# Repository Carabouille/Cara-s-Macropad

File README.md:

# Cara-s-Macropad
my awesome DIY macropad for the hackpad project. Using a screen OLED, 6 switchs, a EC11 and some LEDs

## CAD

I know what you're thinking. and I agree with you it's not very handsome.
BUT I discover this project less than a week ago and with a deadline of January 1 and Christmas, New years.... I don't have time to really make a nice case ;-;

The inserts for the screws do not appear here, but they will of course be added before printing.

However, I am motivated to improve this CAD after the holidays.

I used Solidworks because Fusion is... is Fusion :)

in french we often say "en sah Fusion ca pue sa mère quand meme"

to explain a little bit about what I have in my mind : 

I draw this, and the final version should look like this with the UwU logo on the right

## PCB 
I used KiCad and I tried to make a compact pcb(under 10 x 10cm) with private jokes with my friends and a logo with my nickname "Cara"

IMPORTANT POINT !!!!!
you can see on the electrical sketch that I used some Leds but they do not appear on the PCB that's normal
I added an output for the LEDs below the encoder. I want to use the Leds around the pcb to make an effect that diffuse the light with a fit layer of PLA
So the LEDs should not appear on the PCB.

## Firmware

I'm not good at Pyhton so I asked my friends Pylou to help me with the code
It's pretty simple right now but I would improve everything once I have the card in my hand.
maybe change the language from python to C.

## BOM

Here's the list of parts for my project!

 - 1x Seeed XIAO RP2040
 - 6x Through-hole 1N4148 Diodes
 - 6x MX-Style switches
 - 1x EC11 Rotary encoders
 - 1x 0.91 inch OLED displays
 - 6x Blank DSA keycaps (White)
 - 14x SK6812 MINI-E LEDs
 - 4x M3x16mm screws
 - 4x M3x5mx4mm heatset inserts
 - 1x 3D printed case: not shure about the color
 - 1x PCB

## Special thanks

I want to thank my friend Pylou (love u my boy) for introducing me to the project (a little bit late :)))

thanks to the HackLab community the goatest community 

thanks to my mum for creating me

thanks Guyom, for not doing anything special on this project

thanks David Mercier, to help me to become a great hacker 

Thanks to photosynthesis for creating the oxygen that I breathe

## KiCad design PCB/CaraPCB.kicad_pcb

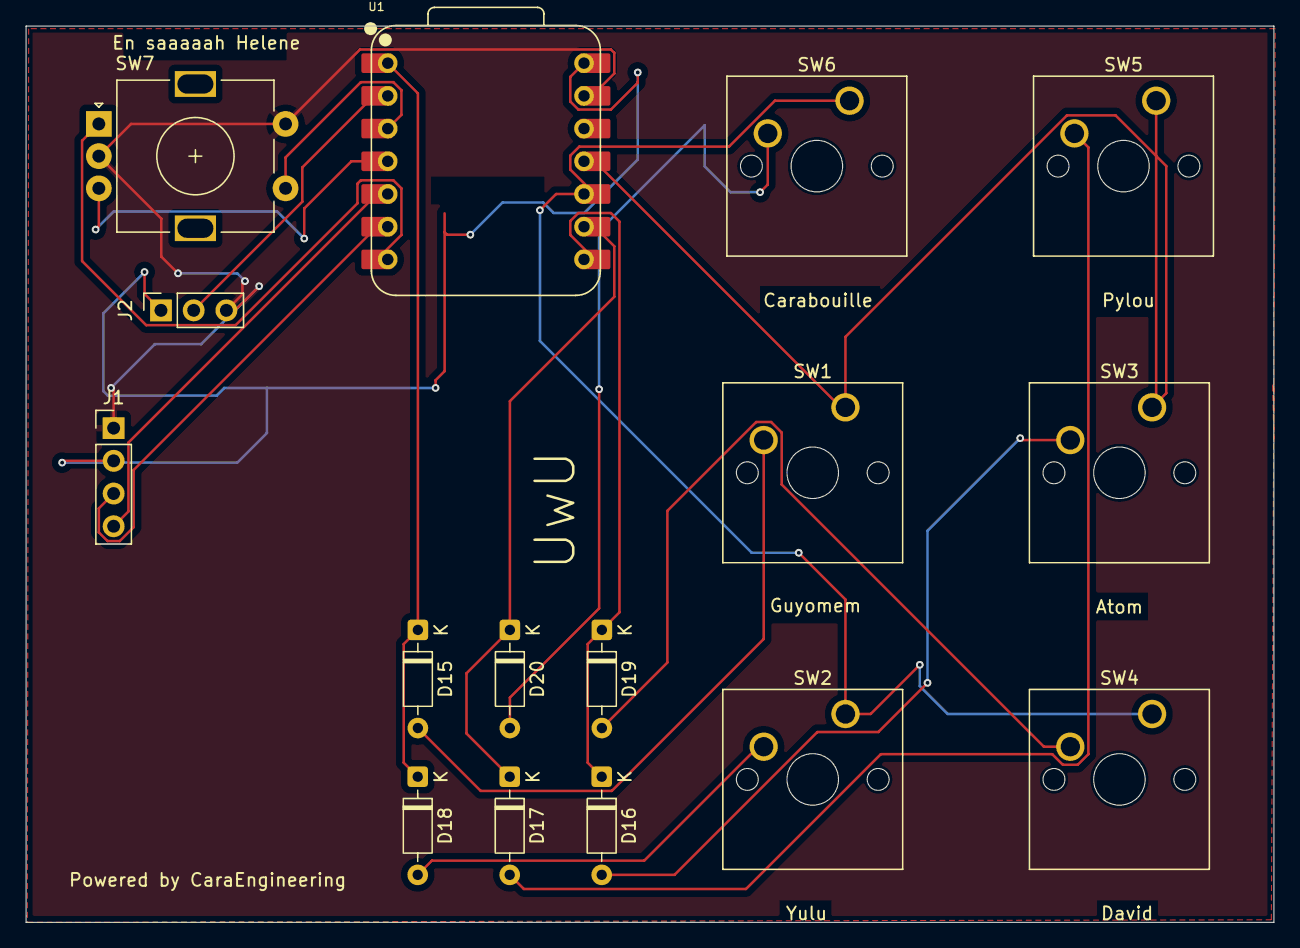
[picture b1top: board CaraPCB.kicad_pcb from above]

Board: 2 copper layers, 96.9 x 69.6 mm, 16 parts (0 on the bottom side), 19 nets.

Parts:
D15, D16, D17, D18, D19, D20: 1N4148; D_DO-35_SOD27_P7.62mm_Horizontal
J1: OLED; PinHeader_1x04_P2.54mm_Vertical
J2: Conn_01x03_Pin; PinSocket_1x03_P2.54mm_Vertical
SW1, SW2, SW3, SW4, SW5, SW6: SW_Push; SW_Cherry_MX_1.00u_PCB
SW7: RotaryEncoder_Switch; RotaryEncoder_Alps_EC11E-Switch_Vertical_H20mm
U1: XIAO-RP2040-DIP

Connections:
GND: J1.1, J2.3, SW7.C, SW7.S2, U1.13 (GND)
unnamed: J2.2, U1.2 (GPIO27/ADC1/A1)
unnamed: D15.2 (A), SW1.2
unnamed: D15.1 (K), D18.1 (K), U1.1 (GPIO26/ADC0/A0)
unnamed: D16.2 (A), SW3.2
unnamed: D16.1 (K), D19.1 (K), U1.8 (GPIO1/RX)
unnamed: D17.2 (A), SW5.2
unnamed: D17.1 (K), D20.1 (K), U1.9 (GPIO2/SCK)
unnamed: D18.2 (A), SW2.2
unnamed: D19.2 (A), SW4.2
unnamed: D20.2 (A), SW6.2
unnamed: J1.3, U1.6 (GPIO7/SCL)
unnamed: J1.4, U1.5 (GPIO6/SDA)
unnamed: SW7.A, U1.7 (GPIO0/TX)
unnamed: SW1.1, SW3.1, SW5.1, U1.11 (GPIO3/MOSI)
unnamed: SW2.1, SW4.1, SW6.1, U1.10 (GPIO4/MISO)
unnamed: SW7.S1, U1.3 (GPIO28/ADC2/A2)
unnamed: SW7.B, U1.4 (GPIO29/ADC3/A3)
VCC: J1.2, J2.1, U1.14 (VBUS)

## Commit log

2025-12-29 Rename case.STEP to Cara's Macropad.STEP
